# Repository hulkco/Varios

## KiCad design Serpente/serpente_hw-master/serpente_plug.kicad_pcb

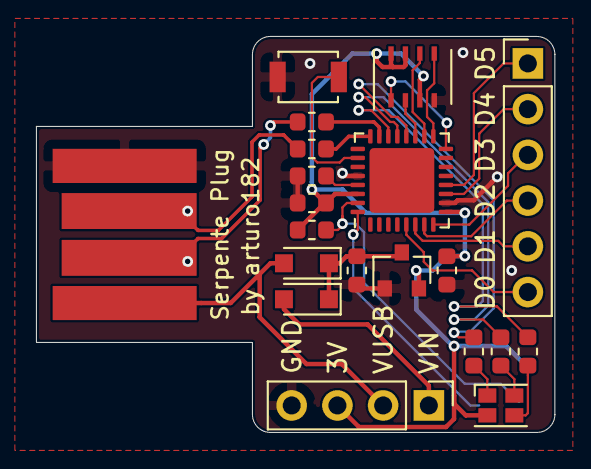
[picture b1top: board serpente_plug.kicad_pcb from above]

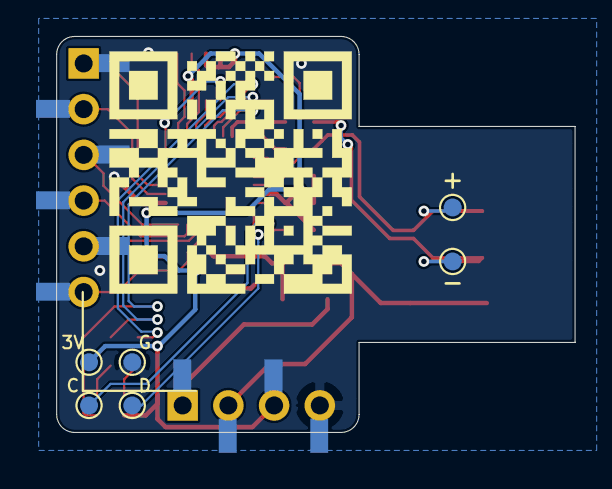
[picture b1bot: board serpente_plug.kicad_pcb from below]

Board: 2 copper layers, 28.8 x 22.0 mm, 27 parts (7 on the bottom side), 29 nets.

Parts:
C1, C4: 1uF; C_0603_1608Metric
C2: 0.1uF; C_0603_1608Metric
C3: 10uF; C_0603_1608Metric
D1, D2: D_Schottky_Small; D_SOD-323_HandSoldering
D3: LED_ARGB; LED_Cree-PLCC4_2x2mm_CW
J1: USB_A; USB_A_Plug_PCB
J2: Serpente_SMD_Reverse
J2#2: Conn_Power; PinHeader_1x04_P2.54mm_Vertical
J3: Conn_GPIO; PinHeader_1x06_P2.54mm_Vertical
R1: 360R; R_0603_1608Metric
R2, R3: 150R; R_0603_1608Metric
R6: 1K; R_0603_1608Metric
R7, R8: 22R; R_0603_1608Metric
SW1: SW_RESET; SW_SPST_B3U-1000P
TP1: TP_SWCLK; TestPoint_Pad_D1.0mm
TP2: TP_SWDIO; TestPoint_Pad_D1.0mm
TP3: TP_VDD; TestPoint_Pad_D1.0mm
TP4: TP_GND; TestPoint_Pad_D1.0mm
TP5: TP_USB_D-; TestPoint_Pad_D1.0mm
TP6: TP_USB_D+; TestPoint_Pad_D1.0mm
U1: GD25Q32CNIGR; USON-8_3x4mm_P0.8mm
U2: MCP1700-3302E_SOT23; SOT-23
U3: ATSAMD21E18A; QFN-32-1EP_5x5mm_P0.5mm_EP3.6x3.6mm

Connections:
+3V3: C2.1, C3.1, D3.4, J2#2.3, R6.2, TP3.1, U1.3, U1.7, U1.8, U2.2, U3.9, U3.30
+5V: C1.2, D1.1, D2.1, U2.3
/FLASH_CS: U1.1, U3.16
/FLASH_MISO: U1.2, U3.19
/FLASH_MOSI: U1.5, U3.17
/FLASH_SCK: U1.6, U3.18
/GPIO0: J3.6, U3.5
/GPIO1: J3.5, U3.6
/GPIO2: J3.4, U3.7
/GPIO3: J3.3, U3.8
/GPIO4: J3.2, U3.11
/GPIO5: J3.1, U3.12
/LED_B: R3.2, U3.21
/LED_G: R2.2, U3.22
/LED_R: R1.2, U3.20
/USB_D+: J1.3, R8.2, TP6.1
/USB_D-: J1.2, R7.2, TP5.1
GND: C1.1, C2.2, C3.2, C4.2, J1.4, J2#2.4, SW1.1, TP4.1, U1.4, U2.1, U3.10, U3.28
unnamed: C4.1, U3.29
unnamed: D3.1, R1.1
unnamed: D3.2, R3.1
unnamed: D3.3, R2.1
unnamed: R6.1, TP1.1, U3.31
unnamed: R7.1, U3.23
unnamed: R8.1, U3.24
unnamed: SW1.2, U3.26
unnamed: TP2.1, U3.32
VBUS: D1.2, J1.1, J2#2.2
VIN: D2.2, J2#2.1

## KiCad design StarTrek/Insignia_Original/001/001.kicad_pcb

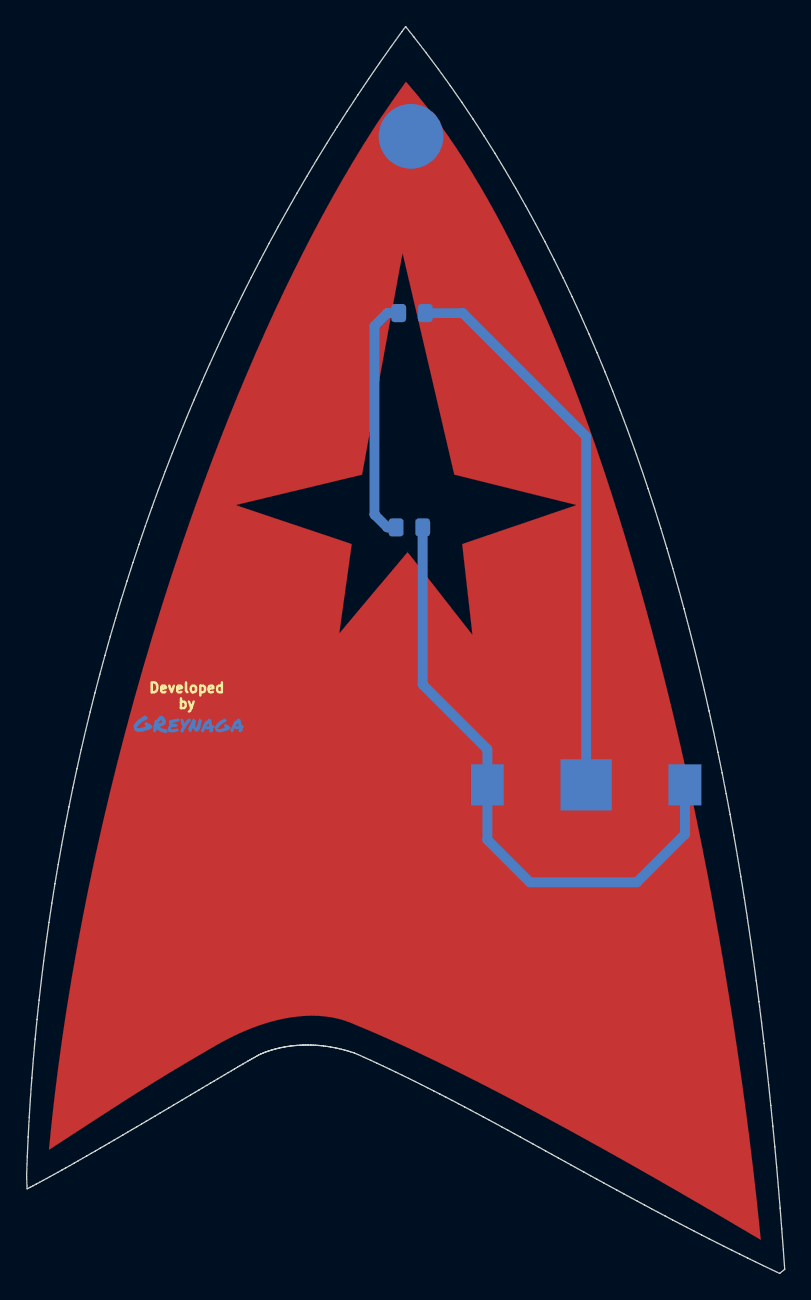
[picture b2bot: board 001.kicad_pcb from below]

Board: 2 copper layers, 58.5 x 96.2 mm, 6 parts (5 on the bottom side), 3 nets.

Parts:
BT1: Battery_3V_Coin; Keystone-CR1220-2894
D1, D2: LED; LED_0805_2012Metric_Pad1.15x1.40mm_HandSolder
Ref**: Val**; TOS_Insignia_100mm_001
U2: Firma; firma_Cu_Mask
U3: PinBase

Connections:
+3V3: BT1.1, D2.2
GND: BT1.2, D1.1
unnamed: D1.2, D2.1
